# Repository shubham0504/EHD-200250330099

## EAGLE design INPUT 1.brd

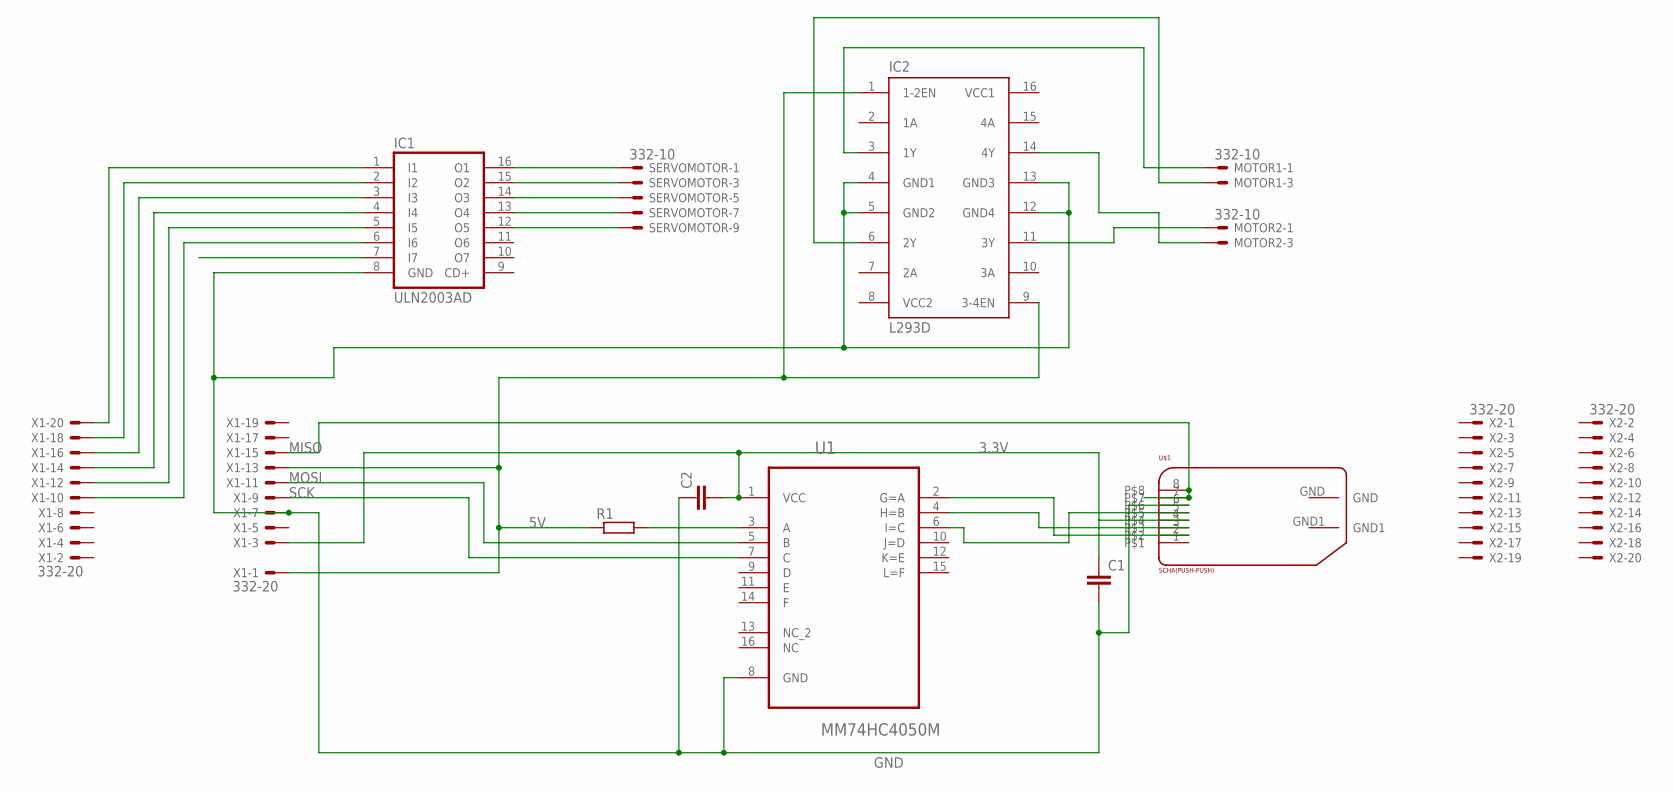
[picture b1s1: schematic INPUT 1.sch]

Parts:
C1, C2: C-EUC0603; C0603
IC1: ULN2003AD; SO16
IC2: L293D; DIL16
MOTOR1, MOTOR2: 332-10
R1: R-EU_R0603; R0603
SERVOMOTOR: 332-10
U1: MM74HC4050M; SOIC127P600X175-16N
U$1: SCHA(PUSH-PUSH); SCHA(PUCH-PUCH_TYPE)
X1, X2: 332-20

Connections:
3.3V: C1.1, C2.2, U1.1 (VCC), U$1.4, X1.3
5V: IC2.1 (1-2EN), IC2.9 (3-4EN), R1.1, X1.1, X1.13
GND: C1.2, C2.1, IC1.8 (GND), IC2.4 (GND1), IC2.5 (GND2), IC2.12 (GND4), IC2.13 (GND3), U1.8 (GND), U$1.6, X1.7
MISO: U$1.7, U$1.8, X1.15
MOSI: U1.5 (B), X1.11
unnamed: U1.2 (G=A), U$1.2
unnamed: U1.4 (H=B), U$1.3
unnamed: R1.2, U1.3 (A)
unnamed: IC1.1 (I1), X1.20
unnamed: U1.6 (I=C), U$1.5
unnamed: IC1.2 (I2), X1.18
unnamed: IC1.3 (I3), X1.16
unnamed: IC1.4 (I4), X1.14
unnamed: IC1.5 (I5), X1.12
unnamed: IC1.6 (I6), X1.10
unnamed: IC1.16 (O1), SERVOMOTOR.1
unnamed: IC1.15 (O2), SERVOMOTOR.3
unnamed: IC1.14 (O3), SERVOMOTOR.5
unnamed: IC1.13 (O4), SERVOMOTOR.7
unnamed: IC1.12 (O5), SERVOMOTOR.9
unnamed: IC2.3 (1Y), MOTOR1.1
unnamed: IC2.6 (2Y), MOTOR1.3
unnamed: IC2.11 (3Y), MOTOR2.1
unnamed: IC2.14 (4Y), MOTOR2.3
SCK: U1.7 (C), X1.9
VCC1: IC2.16 (VCC1)
VCC2: IC2.8 (VCC2)

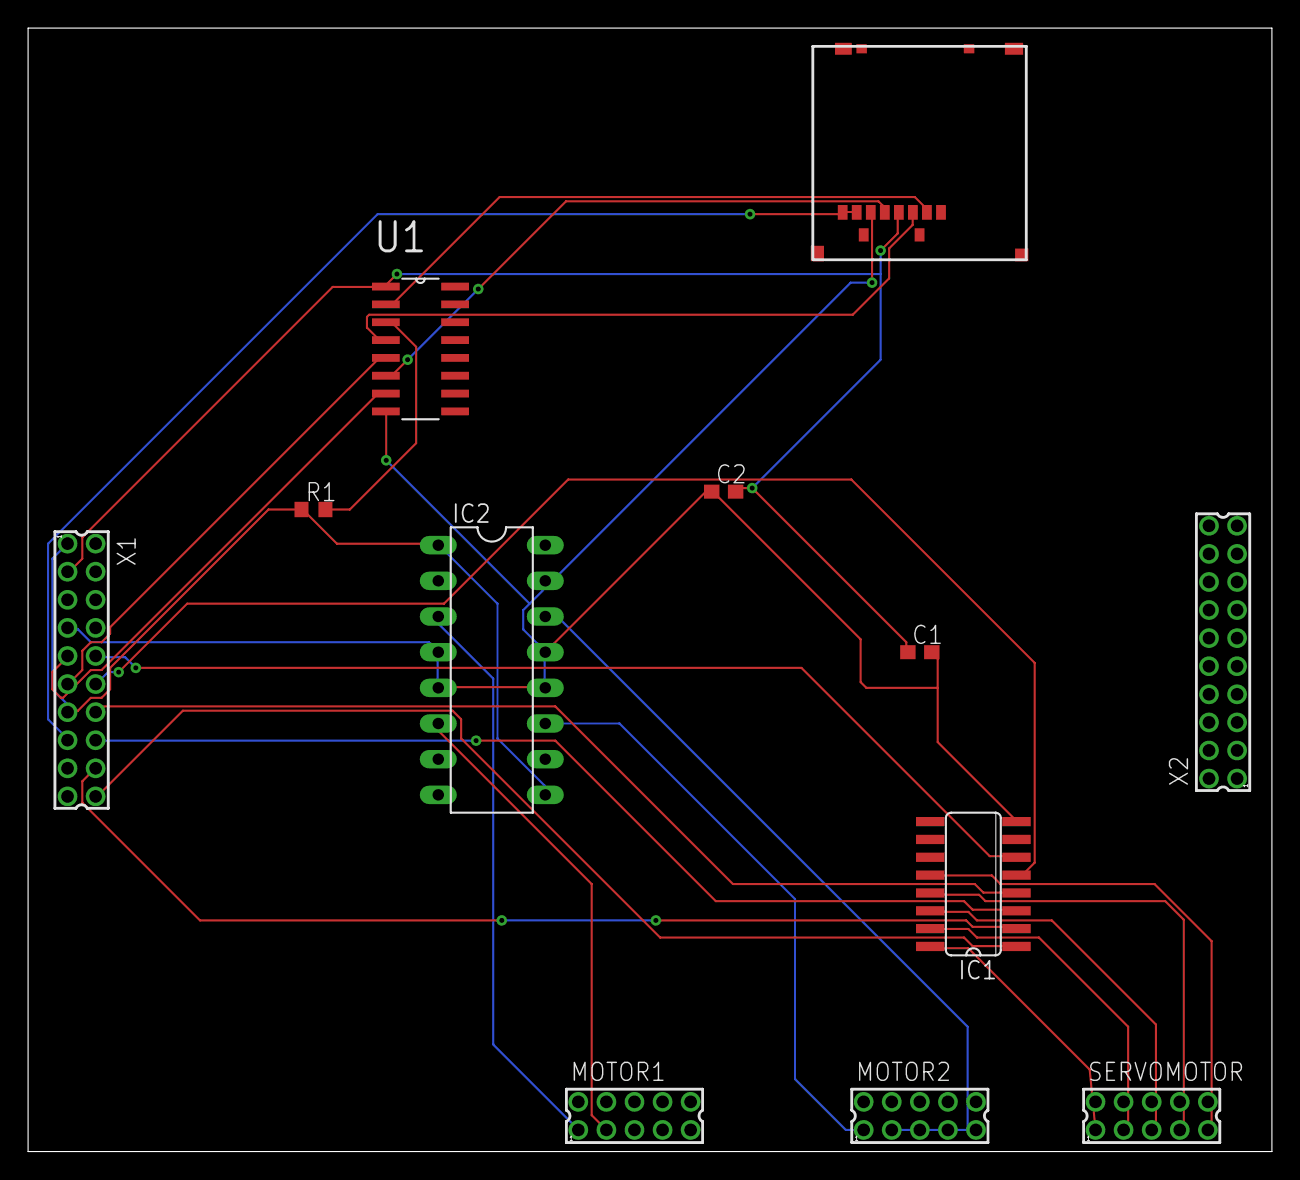
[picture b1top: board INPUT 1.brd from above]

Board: 2 copper layers, 88.6 x 80.0 mm, 12 parts (0 on the bottom side), 25 nets.

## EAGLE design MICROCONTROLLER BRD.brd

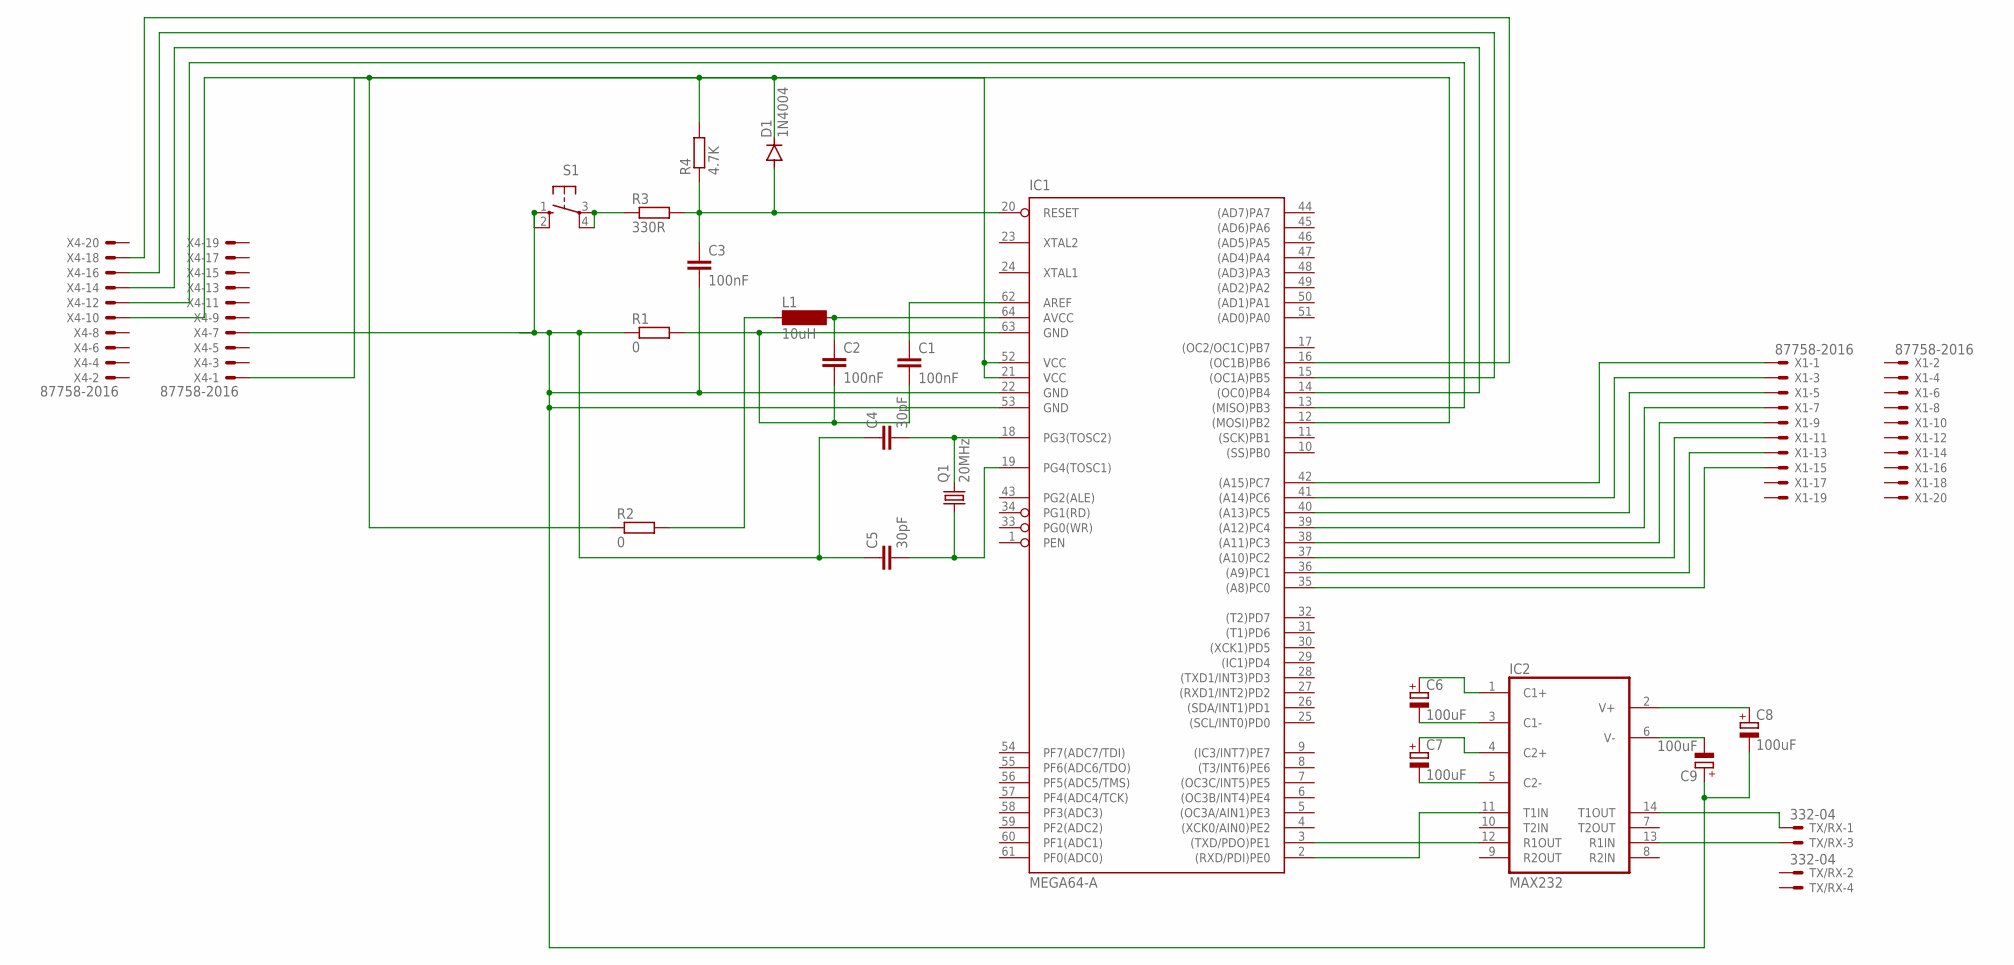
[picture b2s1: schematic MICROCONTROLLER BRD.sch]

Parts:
C1, C2: 100nF; C0402
C3: 100nF; C0603
C4, C5: 30pF; C0603
C6, C7, C8, C9: 100uF; 085CS_1AR
D1: 1N4004; DO41-10
IC1: MEGA64-A; TQFP64
IC2: MAX232; DIL16
L1: 10uH; SM-NE45
Q1: 20MHz; TC26H
R1, R2: 0; R0402
R3: 330R; R0603
R4: 4.7K; R0603
S1: 40-XX; B3F-40XX
TX/RX: 332-04
X1, X4: 87758-2016

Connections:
GND: IC2.15 (GND)
unnamed: R3.1, S1.3, S1.4 (P1)
unnamed: D1.C, IC1.21 (VCC), IC1.52 (VCC), R2.1, R4.2, X4.1
unnamed: C1.1, IC1.62 (AREF)
unnamed: C1.2, C2.2, IC1.63 (GND), R1.2
unnamed: C2.1, IC1.64 (AVCC), L1.2
unnamed: C4.2, IC1.18 (PG3(TOSC2)), Q1.2
unnamed: L1.1, R2.2
unnamed: C3.2, C4.1, C5.1, C8.-, C9.+, IC1.22 (GND), IC1.53 (GND), R1.1, S1.1 (S), S1.2 (S1), X4.7
unnamed: C3.1, D1.A, IC1.20 (RESET), R3.2, R4.1
unnamed: C5.2, IC1.19 (PG4(TOSC1)), Q1.1
unnamed: C6.+, IC2.1 (C1+)
unnamed: C6.-, IC2.3 (C1-)
unnamed: C7.+, IC2.4 (C2+)
unnamed: C7.-, IC2.5 (C2-)
unnamed: C8.+, IC2.2 (V+)
unnamed: C9.-, IC2.6 (V-)
unnamed: IC1.2 ((RXD/PDI)PE0), IC2.11 (T1IN)
unnamed: IC1.3 ((TXD/PDO)PE1), IC2.12 (R1OUT)
unnamed: IC2.14 (T1OUT), TX/RX.1
unnamed: IC2.13 (R1IN), TX/RX.3
unnamed: IC1.42 ((A15)PC7), X1.1
unnamed: IC1.41 ((A14)PC6), X1.3
unnamed: IC1.40 ((A13)PC5), X1.5
unnamed: IC1.39 ((A12)PC4), X1.7
unnamed: IC1.38 ((A11)PC3), X1.9
unnamed: IC1.37 ((A10)PC2), X1.11
unnamed: IC1.36 ((A9)PC1), X1.13
unnamed: IC1.35 ((A8)PC0), X1.15
unnamed: IC1.16 ((OC1B)PB6), X4.18
unnamed: IC1.15 ((OC1A)PB5), X4.16
unnamed: IC1.14 ((OC0)PB4), X4.14
unnamed: IC1.13 ((MISO)PB3), X4.12
unnamed: IC1.12 ((MOSI)PB2), X4.10
VCC: IC2.16 (VCC)

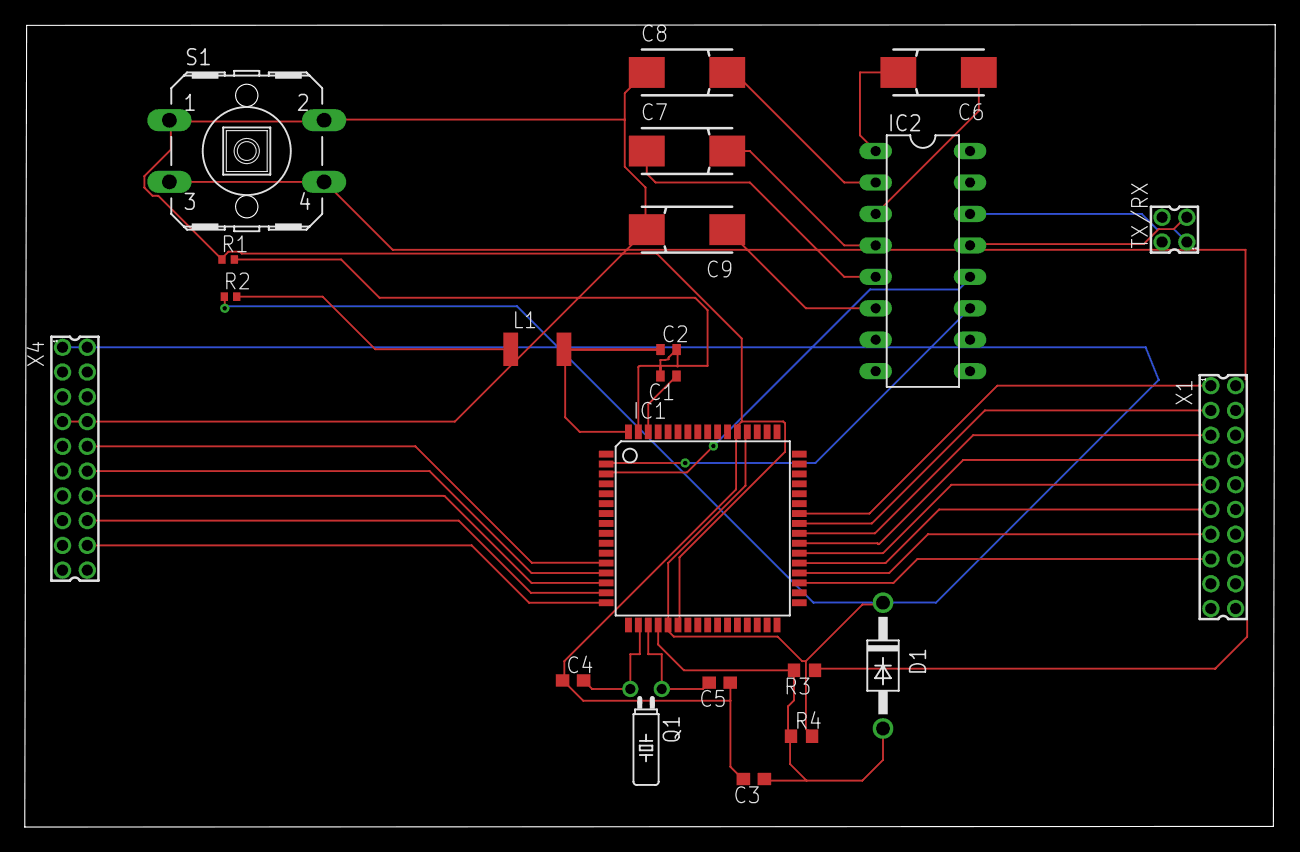
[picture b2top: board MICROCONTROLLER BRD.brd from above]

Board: 2 copper layers, 101.0 x 64.8 mm, 22 parts (0 on the bottom side), 33 nets.

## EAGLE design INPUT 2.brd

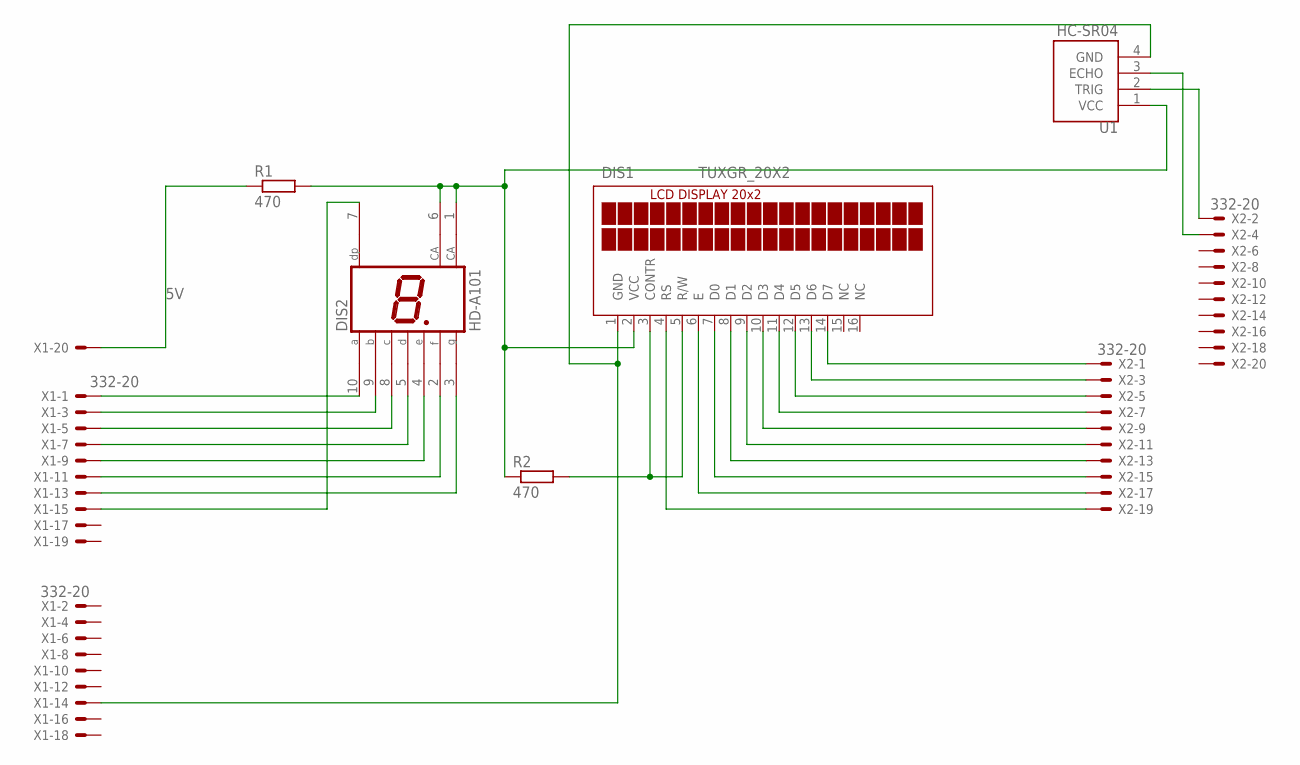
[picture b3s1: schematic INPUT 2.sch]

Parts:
DIS1: TUXGR_20X2
DIS2: HD-A101; HDSP-A
R1, R2: 470; R0603
U1: HC-SR04; XCVR_HC-SR04
X1, X2: 332-20

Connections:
5V: R1.1, X1.20
unnamed: DIS2.10 (A), X1.1
unnamed: DIS2.9 (B), X1.3
unnamed: DIS2.8 (C), X1.5
unnamed: DIS2.5 (D), X1.7
unnamed: DIS2.4 (E), X1.9
unnamed: DIS2.2 (F), X1.11
unnamed: DIS2.3 (G), X1.13
unnamed: DIS2.7 (DP), X1.15
unnamed: DIS1.1 (GND), U1.4 (GND), X1.14
unnamed: DIS1.2 (VCC), DIS2.1 (CA), DIS2.6 (CA), R1.2, R2.1, U1.1 (VCC)
unnamed: DIS1.14 (D7), X2.1
unnamed: DIS1.13 (D6), X2.3
unnamed: DIS1.12 (D5), X2.5
unnamed: DIS1.11 (D4), X2.7
unnamed: DIS1.10 (D3), X2.9
unnamed: DIS1.9 (D2), X2.11
unnamed: DIS1.8 (D1), X2.13
unnamed: DIS1.7 (D0), X2.15
unnamed: DIS1.6 (E), X2.17
unnamed: DIS1.4 (RS), X2.19
unnamed: DIS1.3 (CONTR), DIS1.5 (R/W), R2.2
unnamed: U1.2 (TRIG), X2.2
unnamed: U1.3 (ECHO), X2.4

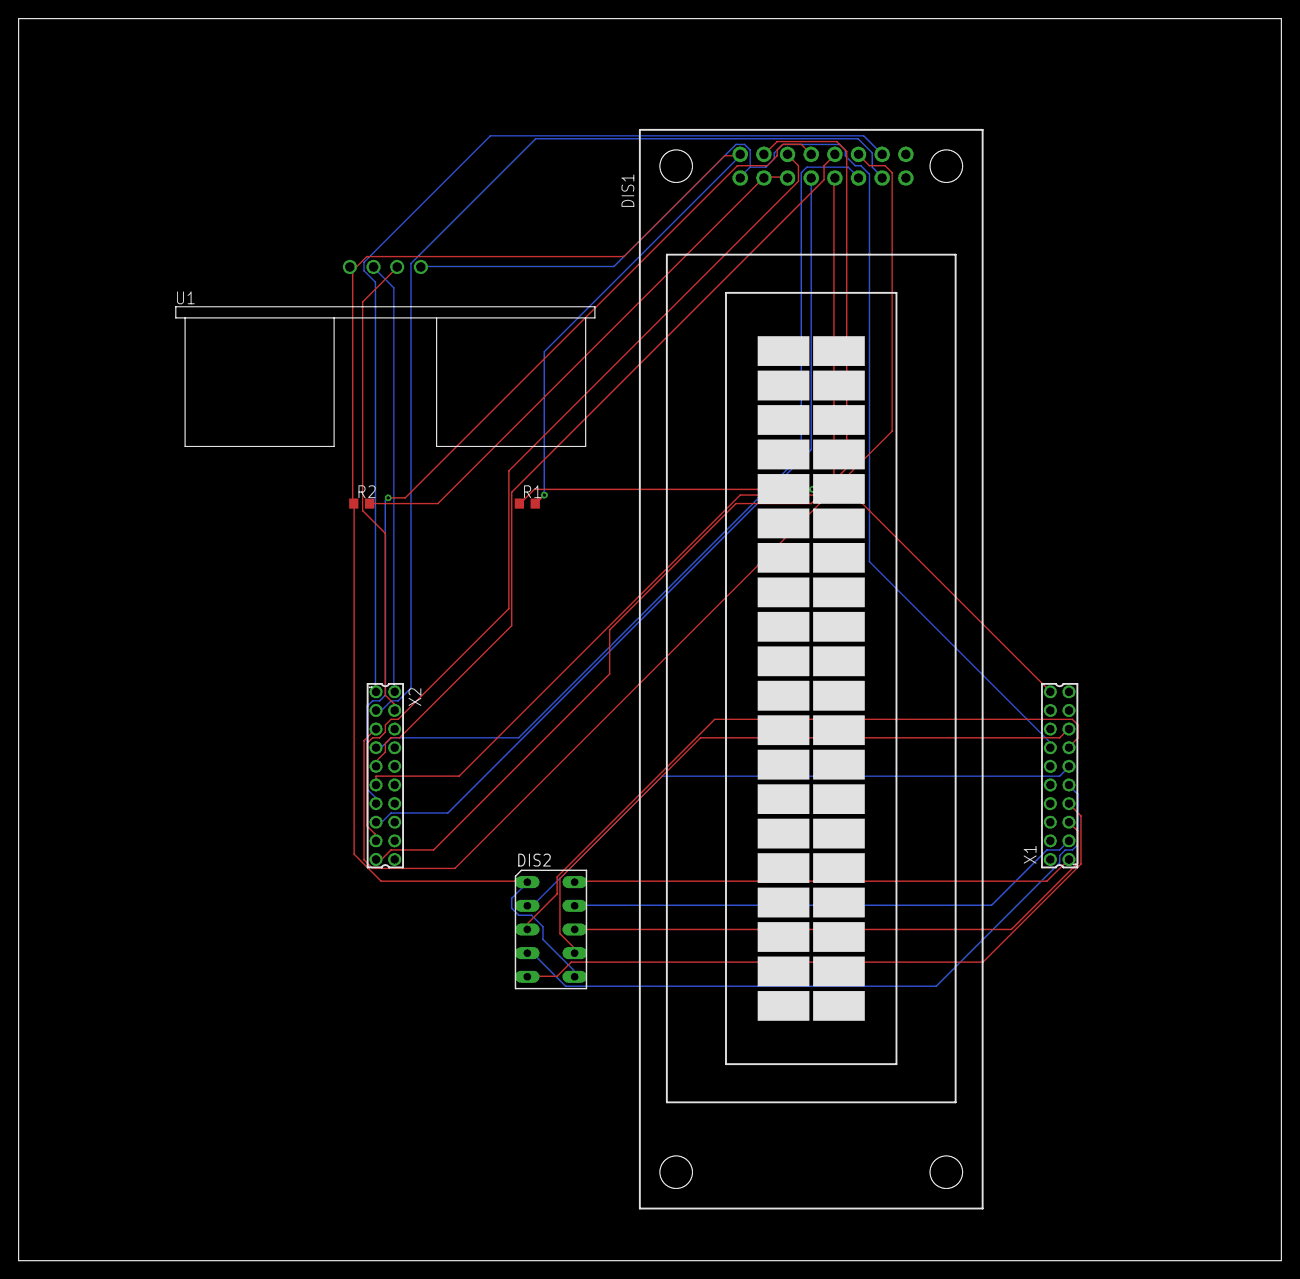
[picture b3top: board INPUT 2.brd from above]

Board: 2 copper layers, 135.6 x 133.3 mm, 7 parts (0 on the bottom side), 24 nets.

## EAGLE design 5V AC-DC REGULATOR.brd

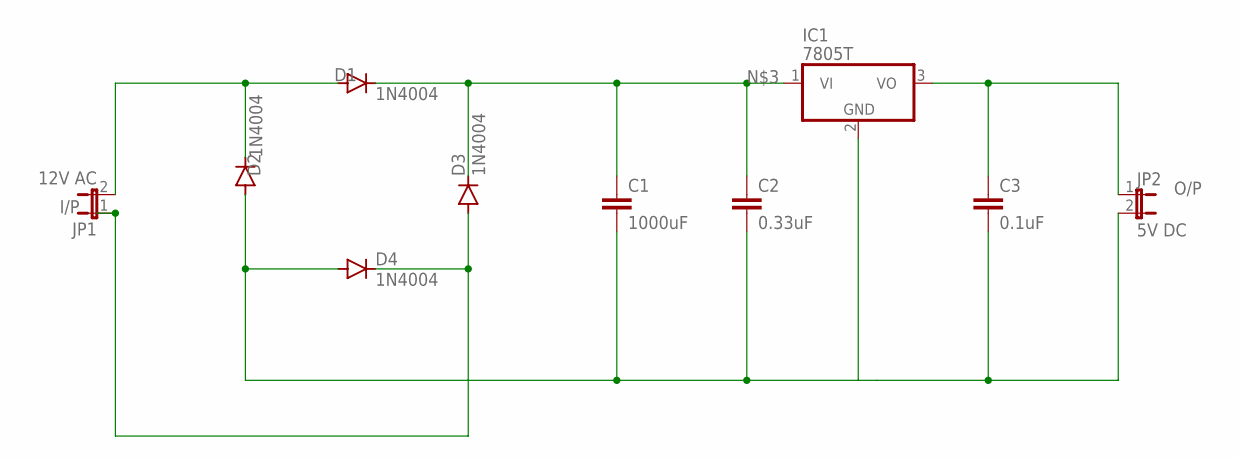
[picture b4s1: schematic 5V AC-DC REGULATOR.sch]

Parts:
C1: 1000uF; C2.5-3
C2: 0.33uF; C2.5-3
C3: 0.1uF; C2.5-3
D1, D2, D3, D4: 1N4004; DO41-10
IC1: 7805T; TO220H
JP1: 12V AC; JP1
JP2: 5V DC; JP1

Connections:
I/P: D3.A, D4.C, JP1.1
unnamed: C1.2, C2.2, C3.2, D2.A, D4.A, IC1.2 (GND), JP2.2
unnamed: C1.1, C2.1, D1.C, D3.C, IC1.1 (VI)
unnamed: D1.A, D2.C, JP1.2
O/P: C3.1, IC1.3 (VO), JP2.1

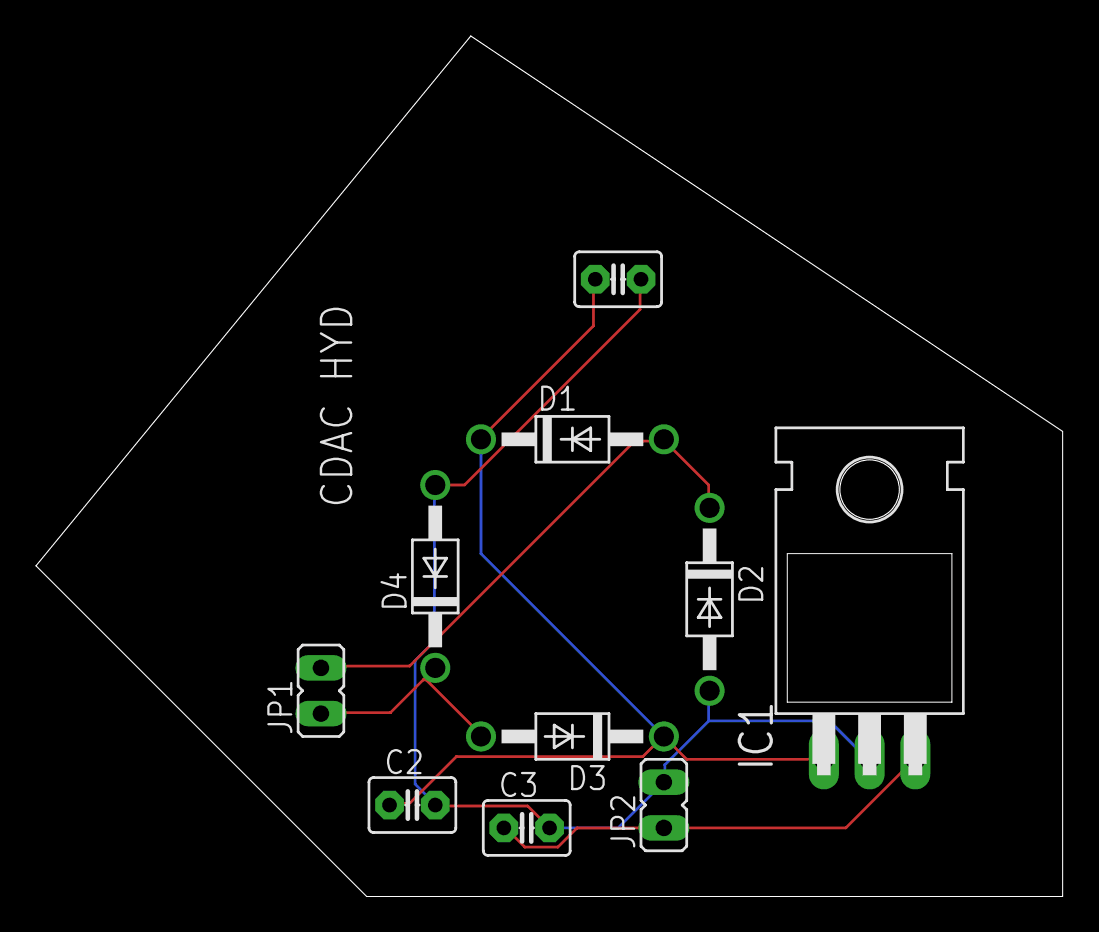
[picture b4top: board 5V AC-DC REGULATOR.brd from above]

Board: 2 copper layers, 57.0 x 47.8 mm, 10 parts (0 on the bottom side), 5 nets.

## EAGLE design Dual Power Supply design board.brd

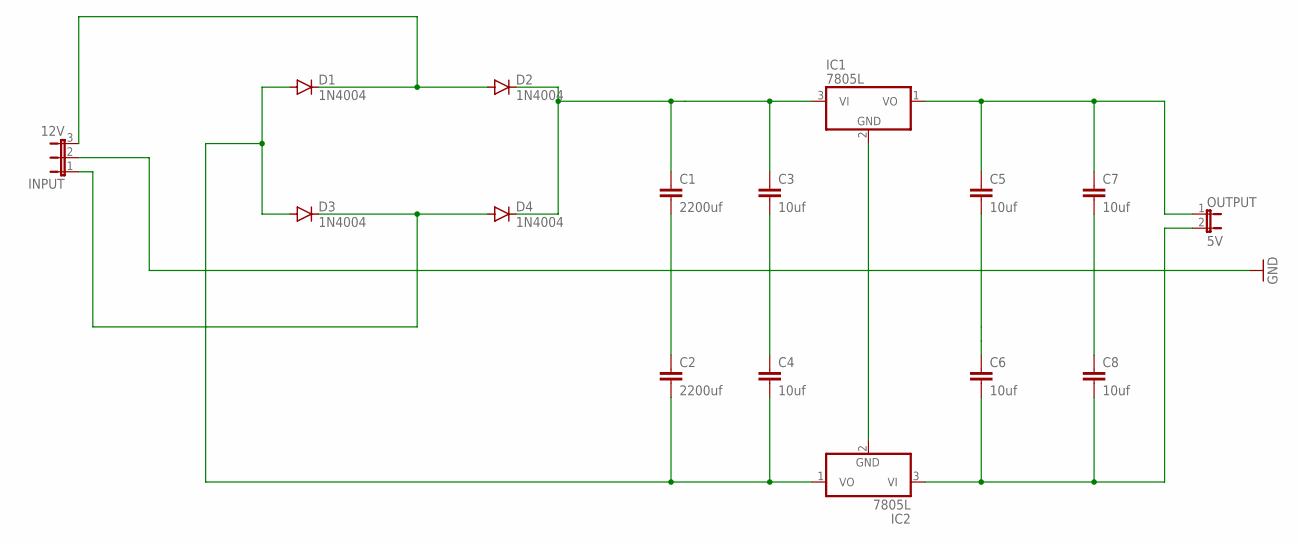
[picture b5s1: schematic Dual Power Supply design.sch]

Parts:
C1, C2: 2200uf; C2.5-3
C3, C4, C5, C6, C7, C8: 10uf; C2.5-3
D1, D2, D3, D4: 1N4004; DO41-10
IC1, IC2: 7805L; TO92
INPUT: 12V; JP2
OUTPUT: 5V; JP1

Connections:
GND: INPUT.2
unnamed: C1.2, C2.1
unnamed: D1.C, D2.A, INPUT.3
unnamed: C1.1, C3.1, D2.C, D4.C, IC1.3 (VI)
unnamed: C2.2, C4.2, D1.A, D3.A, IC2.1 (VO)
unnamed: D3.C, D4.A, INPUT.1
unnamed: C3.2, C4.1
unnamed: C5.1, C7.1, IC1.1 (VO), OUTPUT.1
unnamed: C6.2, C8.2, IC2.3 (VI), OUTPUT.2
unnamed: IC1.2 (GND), IC2.2 (GND)
unnamed: C7.2, C8.1
unnamed: C5.2, C6.1

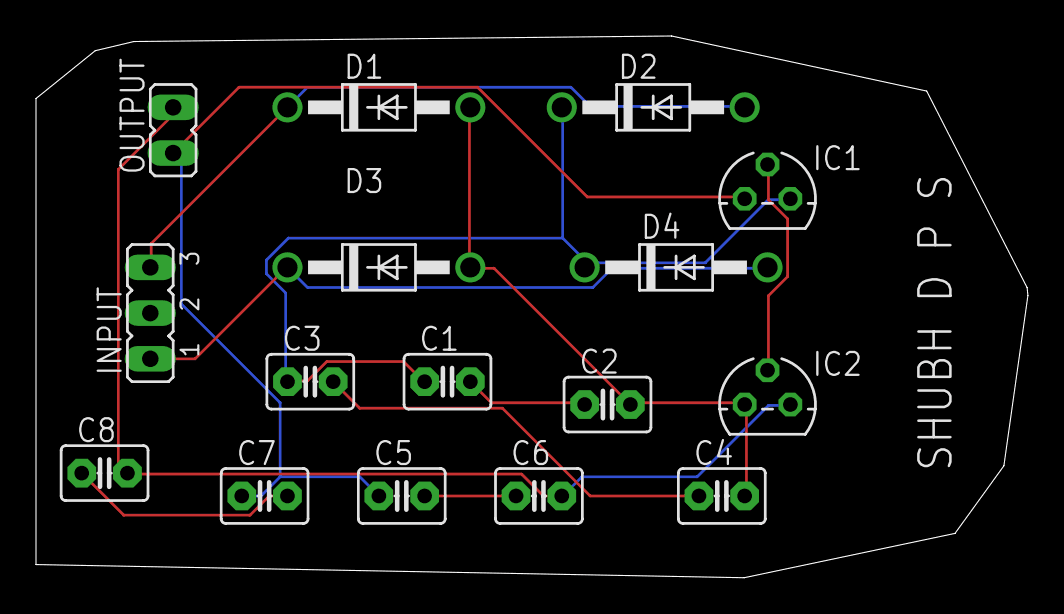
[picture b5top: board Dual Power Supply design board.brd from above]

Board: 2 copper layers, 55.1 x 30.1 mm, 16 parts (0 on the bottom side), 11 nets.
